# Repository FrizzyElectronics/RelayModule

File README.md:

# RelayModule
Relay Module with an opto-isolator connector. It's designed to isolate the 5V board from the 230V/110V noise. It's great for controlling household electronics and apliances with Arduino Boards. It's the entry level to IoT.

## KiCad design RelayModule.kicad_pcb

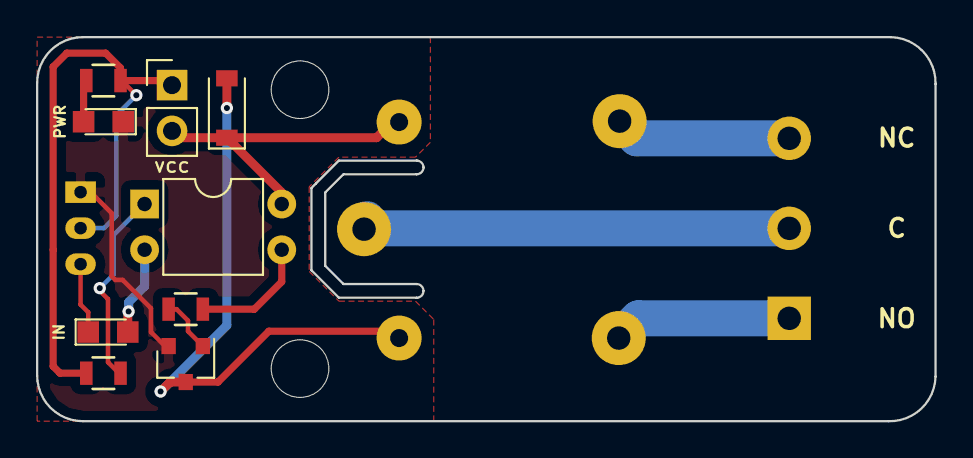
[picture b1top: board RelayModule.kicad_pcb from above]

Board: 2 copper layers, 49.9 x 21.3 mm, 12 parts (0 on the bottom side), 13 nets.

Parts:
D1: LED_POWER; LED_0805
D2: LED_ON; LED_0805
D3: 1N4148; D_SOD-123
JP1: Jumper_NO_Small; Pin_Header_Straight_1x02_Pitch2.54mm
P1: Control_connector; JST_PH_S3B-PH-K_03x2.00mm_Angled
P2: Power_connector; SCREWTERMINAL-5MM-3
Q1: S8050; SOT-23
R1, R2: 1k; R_0805
R3: 510; R_0805
RELAY1: SONGLE_RELAY; Relay_SANYOU_SRD_Series_Form_C
U1: PC817; DIP-4_W7.62mm

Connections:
GND: D1.1, P1.1, Q1.2
IN: D2.1, P1.3
unnamed: D1.2, R1.2
unnamed: D2.2, U1.2
unnamed: D3.1, JP1.2, RELAY1.5, U1.4
unnamed: D3.2, Q1.3, RELAY1.4
unnamed: P2.1, RELAY1.1
unnamed: P2.2, RELAY1.3
unnamed: P2.3, RELAY1.2
unnamed: Q1.1, R3.1
unnamed: R2.1, U1.1
unnamed: R3.2, U1.3
VCC: JP1.1, P1.2, R1.1, R2.2

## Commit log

2017-05-29 License Added
2017-05-29 Esquema en proceso
2017-05-29 Esquema terminado
2017-05-29 Placa terminada, V1.0
2017-06-17 Footprint del borne arreglado
2017-07-09 Solucionado un error en el footprint del transistor S8050
2018-01-20 Gerbers Exportados
    Gerbers exportados para prueba de panelizacion
2018-02-05 logo atomo añadido
2018-02-10 Conector cambiado
2018-02-24 logo movido
2018-03-04 Arbol de librerias cambiado
